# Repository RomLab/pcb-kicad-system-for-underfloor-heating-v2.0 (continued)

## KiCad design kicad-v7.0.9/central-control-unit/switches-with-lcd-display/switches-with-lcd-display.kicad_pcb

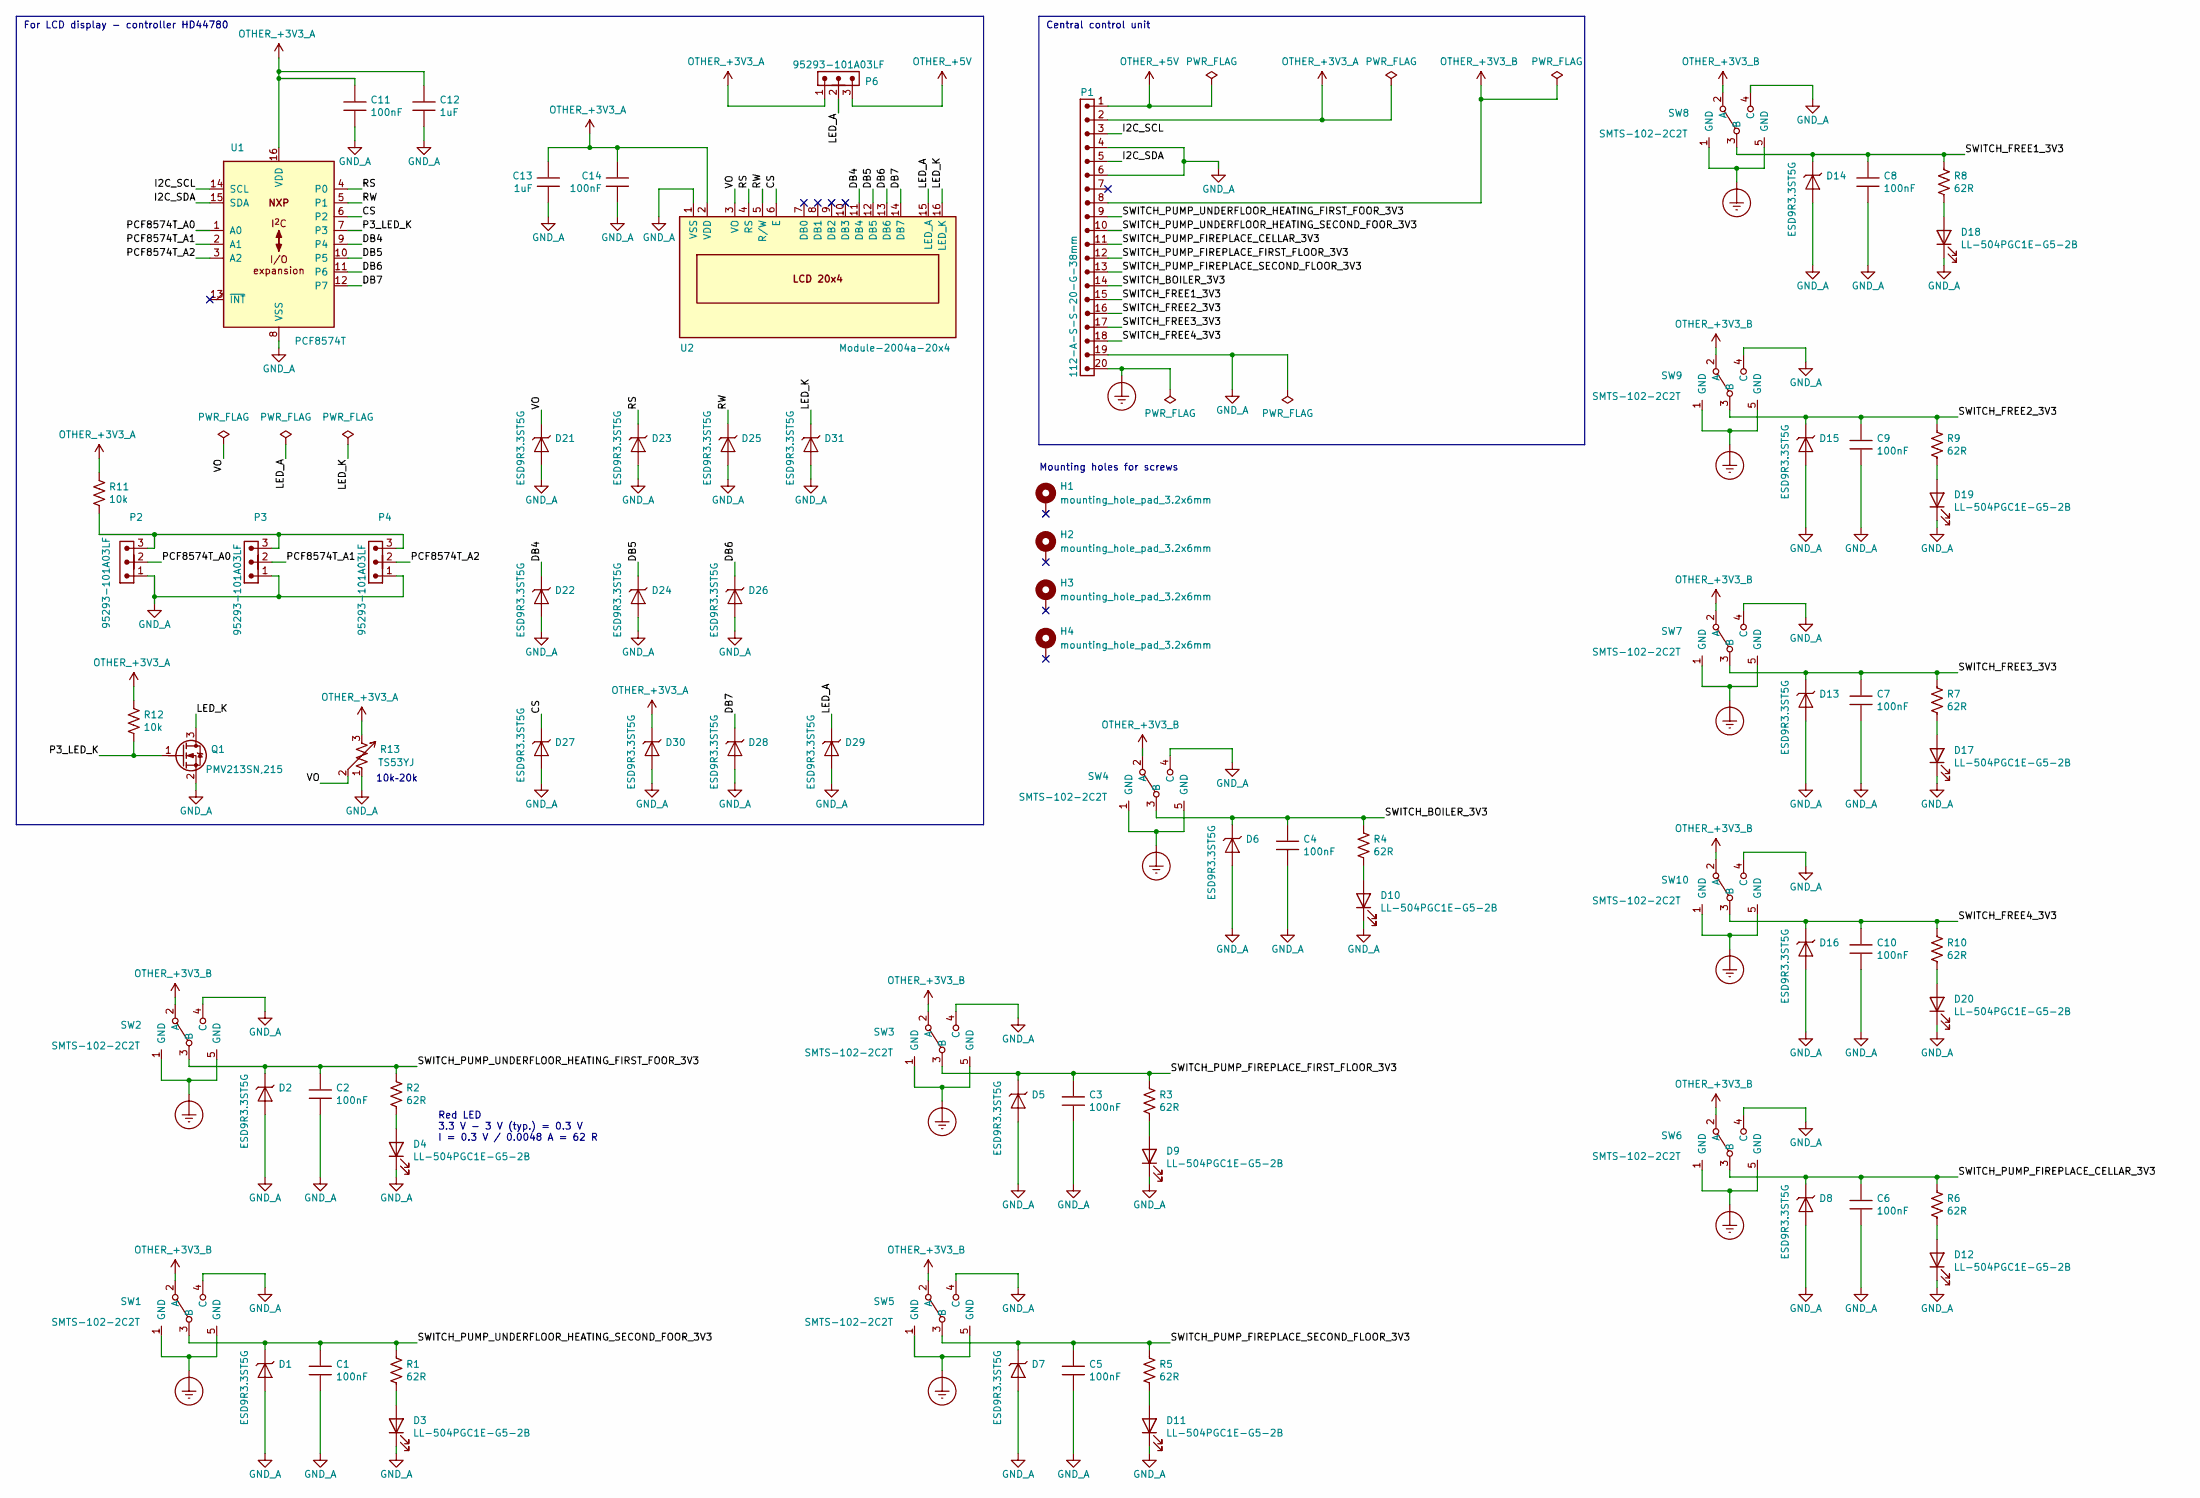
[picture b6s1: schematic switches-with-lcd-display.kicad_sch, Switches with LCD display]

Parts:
C1, C2, C3, C4, C5, C6, C7, C8, C9, C10, C11, C14: 100nF; c_1206
C12, C13: 1uF; c_1206
D1, D2, D5, D6, D7, D8, D13, D14, D15, D16, D21, D22, D23, D24, D25, D26, D27, D28, D29, D30, D31: ESD9R3.3ST5G; sod_923
D3, D4, D9, D10, D11, D12, D17, D18, D19, D20: LL-504PGC1E-G5-2B; led_d5mm_2.54mm
H1, H2, H3, H4: mounting_hole_pad_3.2x6mm
P1: 112-A-S-S-20-G-38mm; 1x20_pin_header_2.54mm_vertical
P2, P3, P4, P6: 95293-101A03LF; 1x3_pin_header_2.54mm_vertical
Q1: PMV213SN,215; sot_23
R1, R2, R3, R4, R5, R6, R7, R8, R9, R10: 62R; r_1206
R11, R12: 10k; r_1206
R13: TS53YJ
SW1, SW2, SW3, SW4, SW5, SW6, SW7, SW8, SW9, SW10: SMTS-102-2C2T
U1: PCF8574T; so_16
U2: Module-2004a-20x4

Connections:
/CS: D27.1 (K), U1.6 (P2), U2.6 (E)
/DB4: D22.1 (K), U1.9 (P4), U2.11 (DB4)
/DB5: D24.1 (K), U1.10 (P5), U2.12 (DB5)
/DB6: D26.1 (K), U1.11 (P6), U2.13 (DB6)
/DB7: D28.1 (K), U1.12 (P7), U2.14 (DB7)
/I2C_SCL: P1.3, U1.14 (SCL)
/I2C_SDA: P1.5, U1.15 (SDA)
/LED_A: D29.1 (K), P6.2, U2.15 (LED_A)
/LED_K: D31.1 (K), Q1.3 (D), U2.16 (LED_K)
/P3_LED_K: Q1.1 (G), R12.2, U1.7 (P3)
/PCF8574T_A0: P2.2, U1.1 (A0)
/PCF8574T_A1: P3.2, U1.2 (A1)
/PCF8574T_A2: P4.2, U1.3 (A2)
/RS: D23.1 (K), U1.4 (P0), U2.4 (RS)
/RW: D25.1 (K), U1.5 (P1), U2.5 (R/W)
/SWITCH_BOILER_3V3: C4.1, D6.1 (K), P1.14, R4.1, SW4.3 (B)
/SWITCH_FREE1_3V3: C8.1, D14.1 (K), P1.15, R8.1, SW8.3 (B)
/SWITCH_FREE2_3V3: C9.1, D15.1 (K), P1.16, R9.1, SW9.3 (B)
/SWITCH_FREE3_3V3: C7.1, D13.1 (K), P1.17, R7.1, SW7.3 (B)
/SWITCH_FREE4_3V3: C10.1, D16.1 (K), P1.18, R10.1, SW10.3 (B)
/SWITCH_PUMP_FIREPLACE_CELLAR_3V3: C6.1, D8.1 (K), P1.11, R6.1, SW6.3 (B)
/SWITCH_PUMP_FIREPLACE_FIRST_FLOOR_3V3: C3.1, D5.1 (K), P1.12, R3.1, SW3.3 (B)
/SWITCH_PUMP_FIREPLACE_SECOND_FLOOR_3V3: C5.1, D7.1 (K), P1.13, R5.1, SW5.3 (B)
/SWITCH_PUMP_UNDERFLOOR_HEATING_FIRST_FOOR_3V3: C2.1, D2.1 (K), P1.9, R2.1, SW2.3 (B)
/SWITCH_PUMP_UNDERFLOOR_HEATING_SECOND_FOOR_3V3: C1.1, D1.1 (K), P1.10, R1.1, SW1.3 (B)
/VO: D21.1 (K), R13.2, U2.3 (VO)
Earth_Protective: P1.20, SW1.1 (GND), SW1.5 (GND), SW2.1 (GND), SW2.5 (GND), SW3.1 (GND), SW3.5 (GND), SW4.1 (GND), SW4.5 (GND), SW5.1 (GND), SW5.5 (GND), SW6.1 (GND), SW6.5 (GND), SW7.1 (GND), SW7.5 (GND), SW8.1 (GND), SW8.5 (GND), SW9.1 (GND), SW9.5 (GND), SW10.1 (GND), SW10.5 (GND)
GND_A: C1.2, C2.2, C3.2, C4.2, C5.2, C6.2, C7.2, C8.2, C9.2, C10.2, C11.1, C12.1, C13.1, C14.1, D1.2 (A), D2.2 (A), D3.1 (K), D4.1 (K), D5.2 (A), D6.2 (A), D7.2 (A), D8.2 (A), D9.1 (K), D10.1 (K), D11.1 (K), D12.1 (K), D13.2 (A), D14.2 (A), D15.2 (A), D16.2 (A), D17.1 (K), D18.1 (K), D19.1 (K), D20.1 (K), D21.2 (A), D22.2 (A), D23.2 (A), D24.2 (A), D25.2 (A), D26.2 (A), D27.2 (A), D28.2 (A), D29.2 (A), D30.2 (A), D31.2 (A), P1.4, P1.6, P1.19, P2.1, P3.1, P4.1, Q1.2 (S), R13.1, SW1.4 (C), SW2.4 (C), SW3.4 (C), SW4.4 (C), SW5.4 (C), SW6.4 (C), SW7.4 (C), SW8.4 (C), SW9.4 (C), SW10.4 (C), U1.8 (VSS), U2.1 (VSS)
unnamed: D3.2 (A), R1.2
unnamed: D4.2 (A), R2.2
unnamed: D9.2 (A), R3.2
unnamed: D10.2 (A), R4.2
unnamed: D11.2 (A), R5.2
unnamed: D12.2 (A), R6.2
unnamed: D17.2 (A), R7.2
unnamed: D18.2 (A), R8.2
unnamed: D19.2 (A), R9.2
unnamed: D20.2 (A), R10.2
unnamed: P2.3, P3.3, P4.3, R11.2
OTHER_+3V3_A: C11.2, C12.2, C13.2, C14.2, D30.1 (K), P1.2, P6.1, R11.1, R12.1, R13.3, U1.16 (VDD), U2.2 (VDD)
OTHER_+3V3_B: P1.8, SW1.2 (A), SW2.2 (A), SW3.2 (A), SW4.2 (A), SW5.2 (A), SW6.2 (A), SW7.2 (A), SW8.2 (A), SW9.2 (A), SW10.2 (A)
OTHER_+5V: P1.1, P6.3

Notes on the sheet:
Mounting holes for screws
Central control unit
For LCD display - controller HD44780
10k–20k
Red LED 3.3 V - 3 V (typ.) = 0.3 V I = 0.3 V / 0.0048 A = 62 R

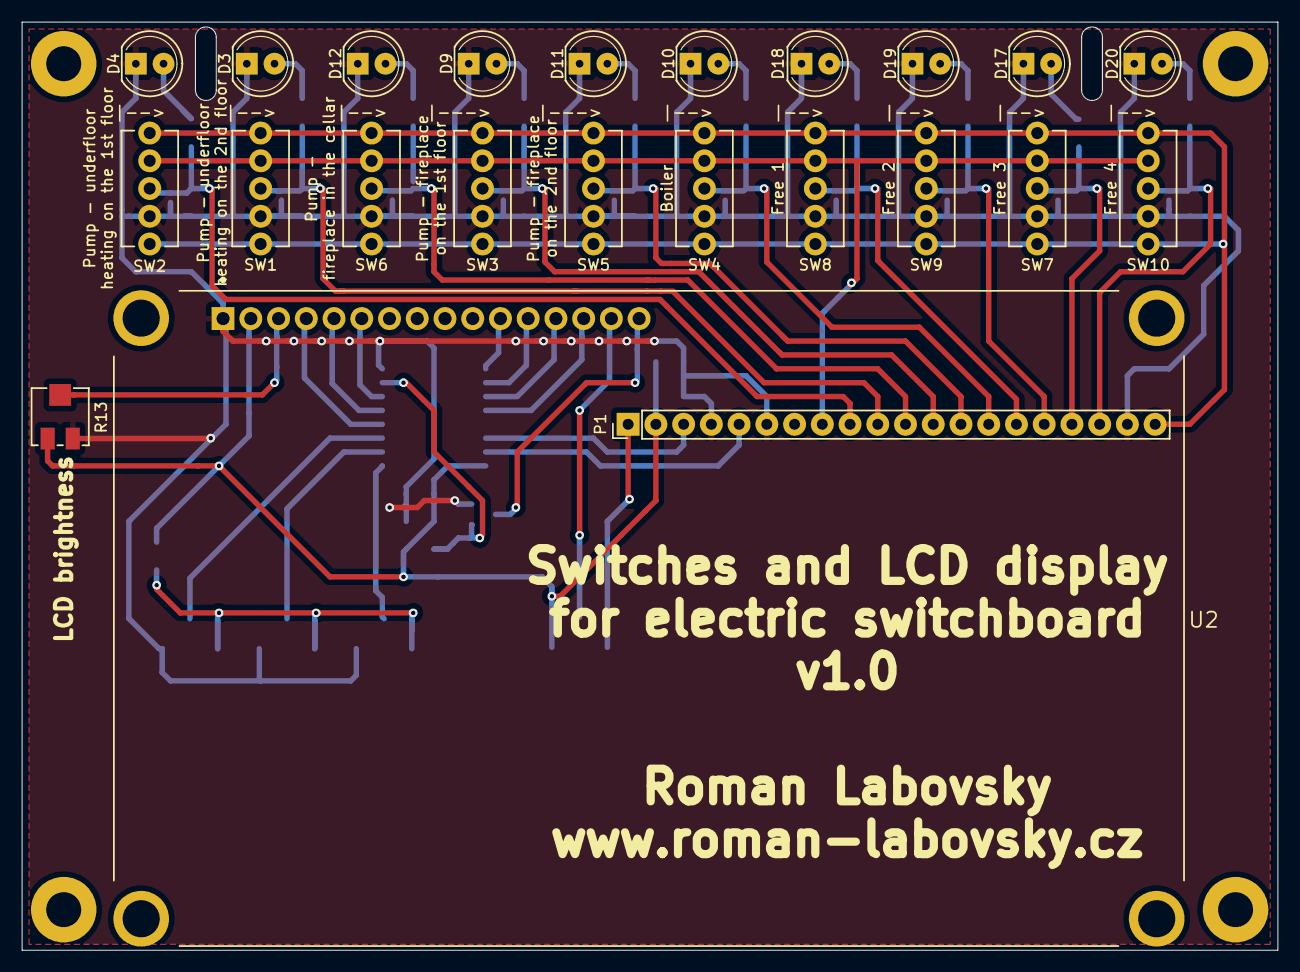
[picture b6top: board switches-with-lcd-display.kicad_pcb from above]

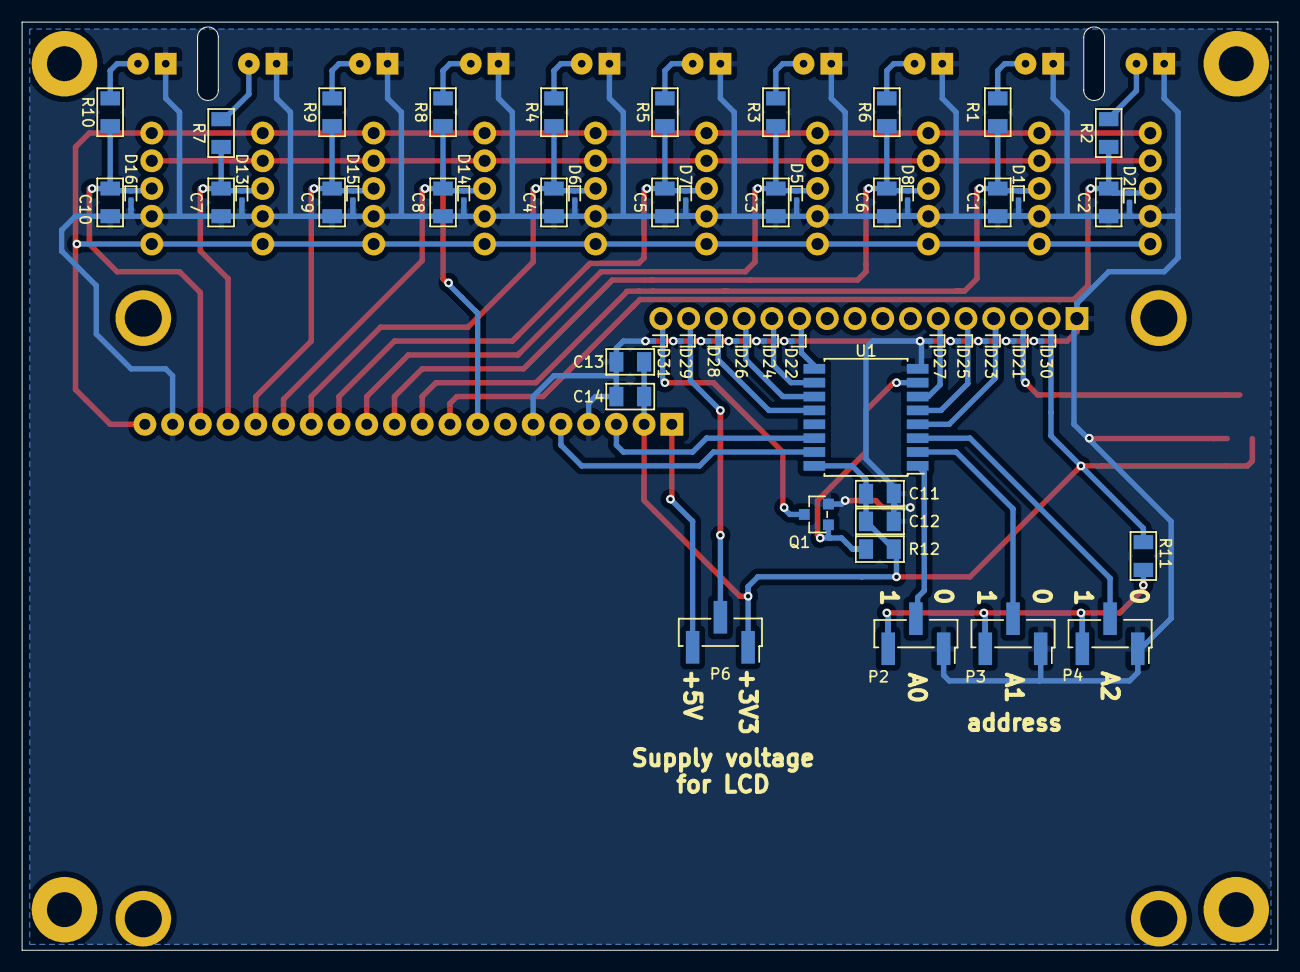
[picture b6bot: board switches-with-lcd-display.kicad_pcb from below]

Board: 2 copper layers, 115.0 x 85.0 mm, 80 parts (53 on the bottom side), 42 nets.

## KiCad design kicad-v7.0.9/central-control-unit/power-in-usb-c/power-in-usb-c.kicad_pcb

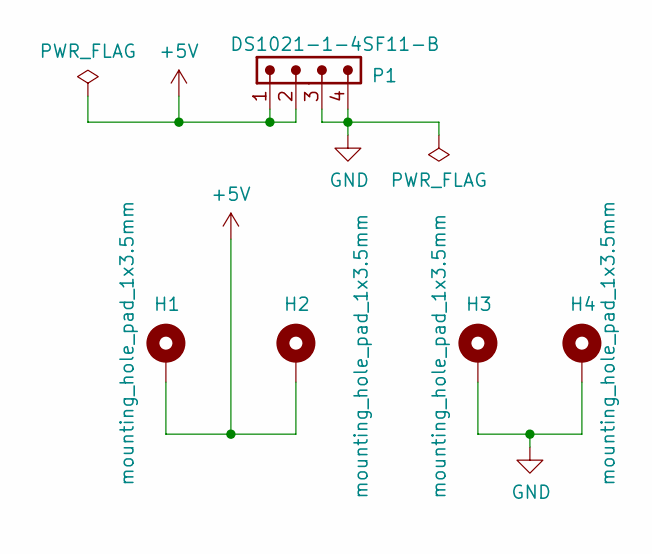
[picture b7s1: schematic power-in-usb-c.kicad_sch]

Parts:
H1, H2, H3, H4: mounting_hole_pad_1x3.5mm
P1: DS1021-1-4SF11-B; 1x4_pin_header_2.54mm_vertical

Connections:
+5V: H1.1, H2.1, P1.1, P1.2
GND: H3.1, H4.1, P1.3, P1.4

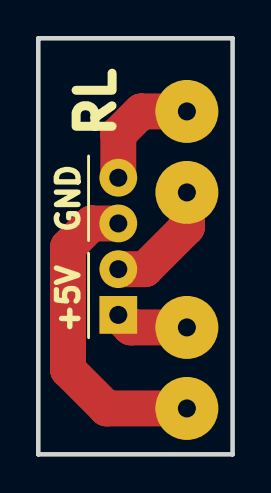
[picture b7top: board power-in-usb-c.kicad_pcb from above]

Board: 2 copper layers, 10.8 x 23.1 mm, 5 parts (1 on the bottom side), 2 nets.

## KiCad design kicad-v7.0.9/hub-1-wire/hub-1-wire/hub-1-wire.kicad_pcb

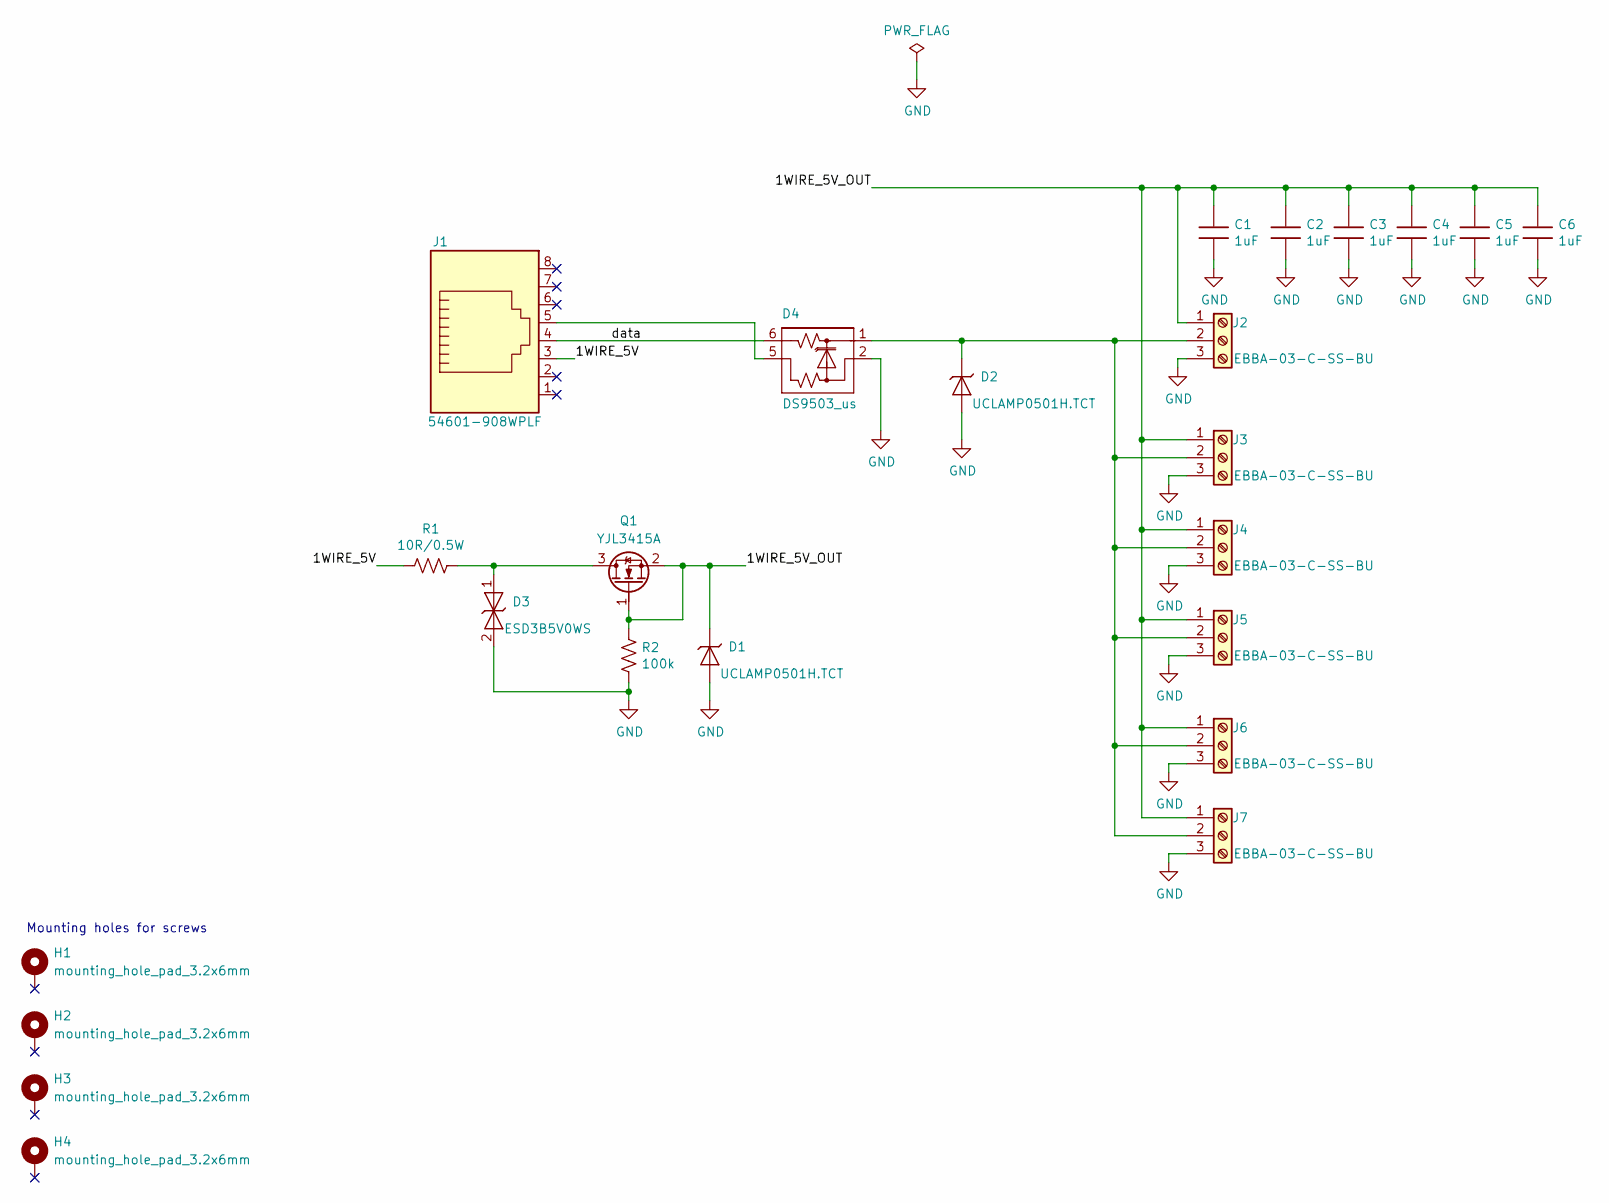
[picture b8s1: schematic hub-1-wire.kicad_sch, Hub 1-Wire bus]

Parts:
C1, C2, C3, C4, C5, C6: 1uF; c_1206
D1, D2: UCLAMP0501H.TCT; sod_523
D3: ESD3B5V0WS; sod_323
D4: DS9503_us; tsoc_6
H1, H2, H3, H4: mounting_hole_pad_3.2x6mm
J1: 54601-908WPLF
J2, J3, J4, J5, J6, J7: EBBA-03-C-SS-BU
Q1: YJL3415A; sot_23
R1: 10R/0.5W; r_1206
R2: 100k; r_1206

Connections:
/1WIRE_5V: J1.3, R1.2
/1WIRE_5V_OUT: C1.1, C2.1, C3.1, C4.1, C5.1, C6.1, D1.1 (K), J2.1, J3.1, J4.1, J5.1, J6.1, J7.1, Q1.1 (G), Q1.2 (S), R2.1
/data: D4.6 (K), J1.4
GND: C1.2, C2.2, C3.2, C4.2, C5.2, C6.2, D1.2 (A), D2.2 (A), D3.2 (A2), D4.2 (A), J2.3, J3.3, J4.3, J5.3, J6.3, J7.3, R2.2
unnamed: D2.1 (K), D4.1 (K), J2.2, J3.2, J4.2, J5.2, J6.2, J7.2
unnamed: D3.1 (A1), Q1.3 (D), R1.1
unnamed: D4.5 (A), J1.5

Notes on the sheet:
Mounting holes for screws

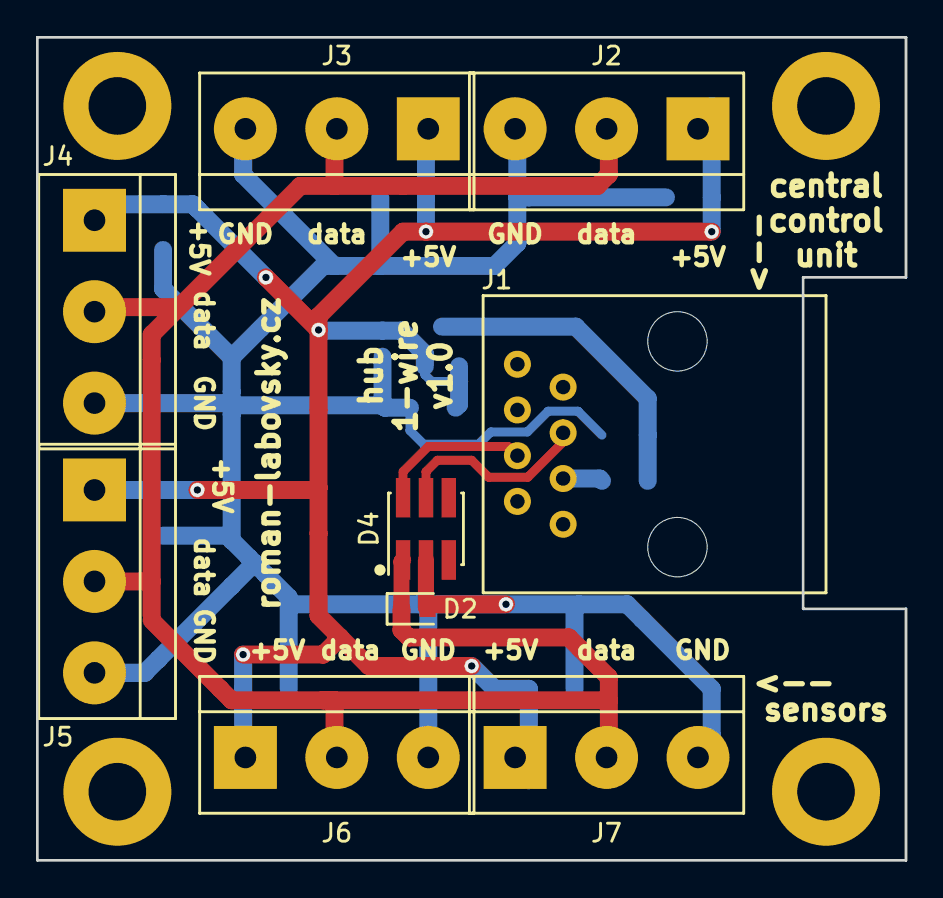
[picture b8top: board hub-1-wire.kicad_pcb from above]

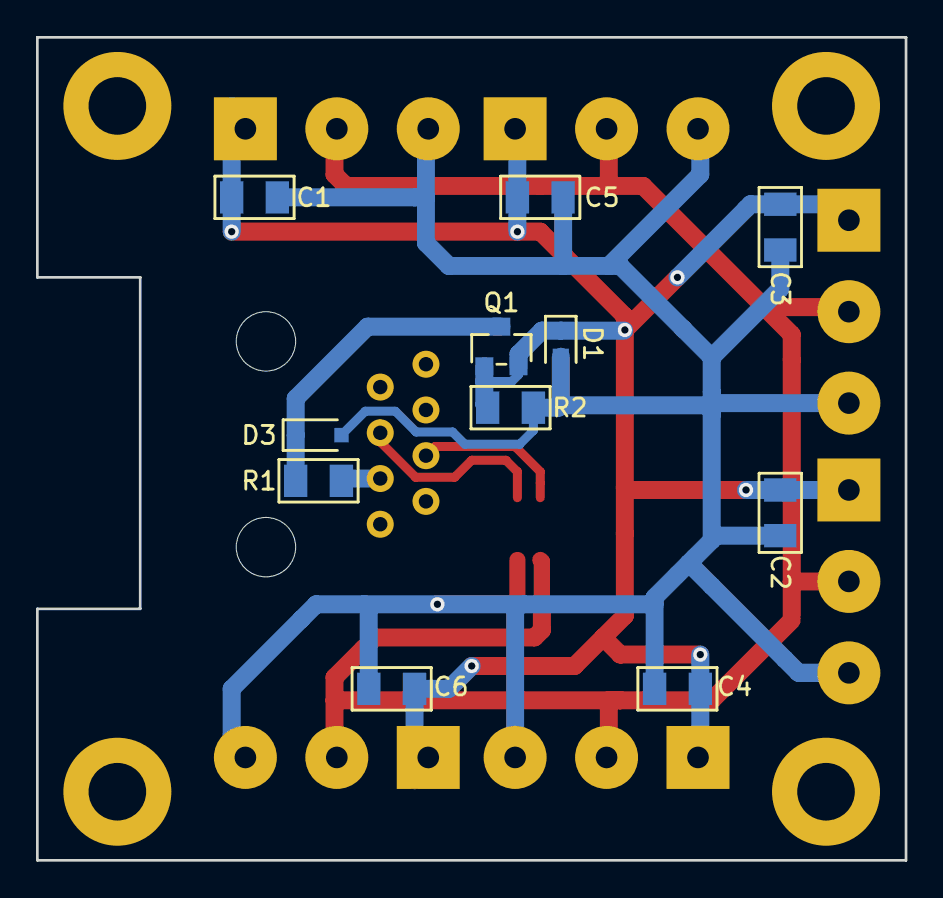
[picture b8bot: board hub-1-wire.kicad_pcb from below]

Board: 2 copper layers, 48.3 x 45.7 mm, 24 parts (11 on the bottom side), 7 nets.

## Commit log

2022-03-30 Adding of signalization by the fireplace.
2022-03-30 Signalization by the fireplace. Adding of 3d view.
2022-03-30 Signalization by the fireplace. Adding of readme.
2022-03-31 Signalization by the fireplace. Adding of files.
2022-05-28 Small changes.
2023-01-25 Adding zone controller pcb.
2023-01-25 Adding central control unit pcb.
2023-01-25 Adding power in usb pcb.
2023-01-25 Adding switches with lcd display pcb.
2023-01-25 Adding testing board pcb.
2023-01-26 Removing of simulation.
2023-06-13 Adding of wall mounted room temperature sensor, the converter USB-UART, 1-Wire hub.
2023-06-13 Remove old version.
2023-07-15 Adding of deployed version and the newest version.
2023-07-15 Change of structure.
2023-07-15 Change of structure and adding of pictures and step files.
2023-08-01 Adding of transistors for LED indication.
2023-09-12 Small changes for zone controller.
2023-10-21 Adding of information about projects.
2023-10-21 Adding of information about project.
2023-10-21 Split project to sheets and adding of description about project.
2023-11-09 Adding of schematics in PDF.
2023-11-09 Rename folders.
2023-11-09 Rename folder.
2023-12-19 Change folder for KiCAD version 5.1.6.
2023-12-21 Adding of zone controller for KiCAD 7.0.9.
2023-12-21 Change info and size page in PCB. Small changes in library.
2023-12-21 Change of Gerber data.
2023-12-21 Update README.md
    Adding info about version KiCAD and libraries.
2023-12-23 Adding of 1-Wire bus hub and connection.
2023-12-23 Change of PDF.
2023-12-23 Adding of signalization by fireplace.
2023-12-23 Adding of testing board.
2023-12-23 Adding of USB to UART converter with module.
2023-12-25 Adding of wall mounted room temperature sensor ethernet.
2023-12-25 Adding of wall mounted room temperature sensor WiFi.
2023-12-28 Zone controller. Change library. Small changes in schematic a PCB.
2023-12-28 Wall mounted room temperature sensor - WiFi. Small changes in schematic a PCB.
2023-12-28 Wall mounted room temperature sensor - ethernet. Change library. Small changes in schematic a PCB.
2023-12-28 USB to UART converter. Change library. Small changes in schematic a PCB.
2023-12-28 Testing board. Change library. Small changes in schematic a PCB.
2023-12-28 Signalization by fireplace. Change library. Small changes in schematic a PCB.
2023-12-28 1-Wire bus hub. Change library. Small changes in schematic a PCB.
2024-01-06 Adding of central control unit.
2024-01-06 Change of components from edited library.
2024-01-06 Change of components from edited library. Change folder structure.
2024-01-06 Change of components from edited library. Adding of schematic in PDF.
2024-01-06 Change of components from edited library. Adding of 3D model.
2024-01-06 Change of components from edited library. Change folder structure. Adding of 3D model.
2024-01-06 Change of components from edited library. Adding of BOM.
2024-01-07 Change components form library. Adding of BOM. Change folder structure.
2024-01-07 Change components form library. Adding of BOM.
